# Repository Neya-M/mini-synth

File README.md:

# mini-synth

A synth but you can only play frequencies received from light, humidity, and temperature sensors.

Schematic:

two of the buttons are upside down for easier routing :P

PCB:

3D View:

BOM:

|Id|Designator|Footprint|Quantity|Designation|Supplier and ref|
|-|-|-|-|-|-|
|1|U4|QFN-20-1EP_4x4mm_P0.5mm_EP2.7x2.7mm|1|MCP23008-xML|https://www.lcsc.com/product-detail/C144211.html?spm=wm.gwc.xh.4.tp___wm.sxq.ssl.gwc&lcsc_vid=FVhWX1RURVBYAgACFQRfXlEDQ1RbBFYDRQNYU1ZfRgQxVlNeT1ZfUF1TR1BYVDsOAxUeFF5JWBYZEEoKFBINSQcJGk4NBhADEA4cHktQQlBADxALGw%3D%3D|
|2|C10|C_0402_1005Metric|1|2.2uF|https://www.lcsc.com/product-detail/C170151.html?s_z=n_q_t_capacitor%25200402&spm=wm.fly.bg.0.xh___wm.ssy.tc.0.tz&lcsc_vid=FVhWX1RURVBYAgACFQRfXlEDQ1RbBFYDRQNYU1ZfRgQxVlNeT1laVVVURlVcXjsOAxUeFF5JWBYZEEoKFBINSQcJGk4NBhYS|
|3|SW3|RotaryEncoder_Alps_EC12E-Switch_Vertical_H20mm|1|volume|https://www.lcsc.com/product-detail/C255515.html?s_z=n_q_t_ec12e&spm=wm.fly.bg.3.stp___wm.ssy.tc.0.tz&lcsc_vid=FVhWX1RURVBYAgACFQRfXlEDQ1RbBFYDRQNYU1ZfRgQxVlNeT1laVFdVQ1BcVTsOAxUeFF5JWBYZEEoKFBINSQcJGk4NBhADEA4cHktQR1BADxALGw%3D%3D|
|4|J4|PinHeader_1x04_P2.54mm_Vertical|1|weaker pins|no part|
|5|"C31|C32|C17|C3|C2|C4|C13|C18|C1|C19|C16|C6"|C_0402_1005Metric|12|100nF|https://www.lcsc.com/product-detail/C60474.html?s_z=n_q_t_capacitor%25200402&spm=wm.fly.bg.0.xh___wm.ssy.tc.0.tz&lcsc_vid=FVhWX1RURVBYAgACFQRfXlEDQ1RbBFYDRQNYU1ZfRgQxVlNeT1laVVVURlVcXjsOAxUeFF5JWBYZEEoKFBINSQcJGk4NBhYS|
|6|"R19|R5|R11|R8|R6"|R_0402_1005Metric|5|10K|https://www.lcsc.com/product-detail/C60490.html?s_z=n_q_t_resistor%25200402&spm=wm.fly.bg.0.xh___wm.ssy.tc.0.tz&lcsc_vid=FVhWX1RURVBYAgACFQRfXlEDQ1RbBFYDRQNYU1ZfRgQxVlNeT1laVFFRTlRWUDsOAxUeFF5JWBYZEEoKFBINSQcJGk4NBhADEA4cHktXRlVcSQwSGg0%3D|
|7|"C8|C9|C7"|C_0402_1005Metric|3|1uF|https://www.lcsc.com/product-detail/C87145.html?s_z=n_q_t_capacitor%25200402&spm=wm.fly.bg.0.xh___wm.ssy.tc.0.tz&lcsc_vid=FVhWX1RURVBYAgACFQRfXlEDQ1RbBFYDRQNYU1ZfRgQxVlNeT1laVVVURlVcXjsOAxUeFF5JWBYZEEoKFBINSQcJGk4NBhYS|
|8|"REF**|REF**|REF**"|capacitive touch button 10mm|3|capacitive touch button 10mm|no part|
|9|R21|SW-TH_PRS11R-415F-S103B1|1|20K|https://www.lcsc.com/product-detail/C17371045.html?spm=wm.gwc.xh.9.cbm___wm.sxq.ssl.gwc&lcsc_vid=FVhWX1RURVBYAgACFQRfXlEDQ1RbBFYDRQNYU1ZfRgQxVlNeT1ZfUF1TR1BYVDsOAxUeFF5JWBYZEEoKFBINSQcJGk4NBhADEA4cHktQQlBADxALGw%3D%3D|
|10|R1|R_LDR_5.1x4.3mm_P3.4mm_Vertical|1|R_Photo|https://www.lcsc.com/product-detail/C125630.html?spm=wm.gwc.xh.10.cbm___wm.sxq.ssl.gwc&lcsc_vid=FVhWX1RURVBYAgACFQRfXlEDQ1RbBFYDRQNYU1ZfRgQxVlNeT1ZfUF1TR1BYVDsOAxUeFF5JWBYZEEoKFBINSQcJGk4NBhADEA4cHktQQlBADxALGw%3D%3D|
|11|U7|WQFN-16-1EP_3x3mm_P0.5mm_EP1.6x1.6mm_ThermalVias|1|TPA6132A2RTE|https://www.lcsc.com/product-detail/C69901.html?s_z=n_q_TPA6132A2RTE&spm=wm.fly.bg.0.xh&lcsc_vid=FVhWX1RURVBYAgACFQRfXlEDQ1RbBFYDRQNYU1ZfRgQxVlNeT1hcUFRSTlNfUjsOAxUeFF5JWBYZEEoKFBINSQcJGk4eFQsCAgIaSgADAwAHC0slQlRfV1xfR1RADxALGw%3D%3D|
|12|SW2|RotaryEncoder_Alps_EC12E-Switch_Vertical_H20mm|1|pitch|https://www.lcsc.com/product-detail/C255515.html?s_z=n_q_t_ec12e&spm=wm.fly.bg.3.stp___wm.ssy.tc.0.tz&lcsc_vid=FVhWX1RURVBYAgACFQRfXlEDQ1RbBFYDRQNYU1ZfRgQxVlNeT1laVFdVQ1BcVTsOAxUeFF5JWBYZEEoKFBINSQcJGk4NBhADEA4cHktQR1BADxALGw%3D%3D|
|13|SW14|SW-TH_RKJXL100401V|1|SW_Rotary_1x8_MP|https://www.lcsc.com/product-detail/C160838.html?spm=wm.gwc.xh.3.tp___wm.sxq.ssl.gwc&lcsc_vid=FVhWX1RURVBYAgACFQRfXlEDQ1RbBFYDRQNYU1ZfRgQxVlNeT1ZfUF1TR1BYVDsOAxUeFF5JWBYZEEoKFBINSQcJGk4NBhADEA4cHktQQlBADxALGw%3D%3D|
|14|"C11|C12|C5"|C_0402_1005Metric|3|4.7uF|https://www.lcsc.com/product-detail/C368809.html?s_z=n_q_t_capacitor%25200402&spm=wm.fly.bg.2.xh___wm.ssy.tc.0.tz&lcsc_vid=FVhWX1RURVBYAgACFQRfXlEDQ1RbBFYDRQNYU1ZfRgQxVlNeT1laVVVURlVcXjsOAxUeFF5JWBYZEEoKFBINSQcJGk4NBhYS|
|15|C25|C_0402_1005Metric|1|4.7uF|https://www.lcsc.com/product-detail/C368809.html?s_z=n_q_t_capacitor%25200402&spm=wm.fly.bg.2.xh___wm.ssy.tc.0.tz&lcsc_vid=FVhWX1RURVBYAgACFQRfXlEDQ1RbBFYDRQNYU1ZfRgQxVlNeT1laVVVURlVcXjsOAxUeFF5JWBYZEEoKFBINSQcJGk4NBhYS|
|16|SW7|SW-SMD_L6.1-W3.7-LS8.0-1|1|BOOT|https://www.lcsc.com/product-detail/C49234126.html?spm=wm.gwc.xh.0.tp___wm.sxq.ssl.gwc&lcsc_vid=FVhWX1RURVBYAgACFQRfXlEDQ1RbBFYDRQNYU1ZfRgQxVlNeT1ZfUF1TR1BYVDsOAxUeFF5JWBYZEEoKFBINSQcJGk4NBhADEA4cHktQQlBADxALGw%3D%3D|
|17|"R13|R12|R9|R7"|R_0402_1005Metric|4|15K|https://www.lcsc.com/product-detail/C2909322.html?s_z=n_q_t_resistor%25200402&spm=wm.fly.bg.0.stp___wm.ssy.tc.0.tz&lcsc_vid=FVhWX1RURVBYAgACFQRfXlEDQ1RbBFYDRQNYU1ZfRgQxVlNeT1laVFFRTlRWUDsOAxUeFF5JWBYZEEoKFBINSQcJGk4NBhADEA4cHktXRlVcSQwSGg0%3D|
|18|"D8|D3|D1|D5|D4|D7|D6|D2"|LED-SMD_4P-L3.2-W2.8-LS5.9_SK6812MINI-E|8|SK6812|https://www.lcsc.com/product-detail/C5149201.html?s_z=n_q_l_SK6812%2520mini%2520e&spm=wm.fly.bg.9.stp___wm.ssy.ml.0-0.ent&lcsc_vid=FVhWX1RURVBYAgACFQRfXlEDQ1RbBFYDRQNYU1ZfRgQxVlNeT1hcUV1XQ1ZdUzsOAxUeFF5JWBYZEEoKFBINSQcJGk4NBhADEA4cHktSR1dADxALGw%3D%3D|
|19|U6|TSSOP-14_L5.0-W4.4-P0.65-LS6.4-BL|1|"74HCT125PW|118"|https://www.lcsc.com/product-detail/C131316.html?spm=wm.gwc.xh.10.cbm___wm.sxq.ssl.gwc&lcsc_vid=FVhWX1RURVBYAgACFQRfXlEDQ1RbBFYDRQNYU1ZfRgQxVlNeT1hcUVNRQVZYUTsOAxUeFF5JWBYZEEoKFBINSQcJGk4NBhYS|
|20|J1|USB-C-SMD_G-SWITCH_GT-USB-7010ASV|1|USB_C_Receptacle_USB2.0_14P|https://www.lcsc.com/product-detail/C2988369.html?spm=wm.gwc.xh.2.cbm___wm.sxq.ssl.gwc&lcsc_vid=FVhWX1RURVBYAgACFQRfXlEDQ1RbBFYDRQNYU1ZfRgQxVlNeT1ZfUF1TR1BYVDsOAxUeFF5JWBYZEEoKFBINSQcJGk4NBhADEA4cHktQQlBADxALGw%3D%3D|
|21|SW1|KEY-TH_L12.0-W3.3-P5.00|1|reset|https://www.lcsc.com/product-detail/C2888728.html?spm=wm.gwc.xh.8.tp___wm.sxq.ssl.gwc&lcsc_vid=FVhWX1RURVBYAgACFQRfXlEDQ1RbBFYDRQNYU1ZfRgQxVlNeT1ZfUF1TR1BYVDsOAxUeFF5JWBYZEEoKFBINSQcJGk4NBhADEA4cHktQQlBADxALGw%3D%3D|
|22|R20|R_0402_1005Metric|1|330|https://www.lcsc.com/product-detail/C105875.html?s_z=n_q_t_resistor%25200402&spm=wm.fly.bg.0.xh___wm.ssy.tc.0.tz&lcsc_vid=FVhWX1RURVBYAgACFQRfXlEDQ1RbBFYDRQNYU1ZfRgQxVlNeT1laVFFRTlRWUDsOAxUeFF5JWBYZEEoKFBINSQcJGk4NBhADEA4cHktXRlVcSQwSGg0%3D|
|23|"D10|D16|D9|D11|D14|D12|D13|D17|D15"|D_0402_1005Metric|9|D|https://www.lcsc.com/product-detail/C28646371.html?s_z=n_q_t_diode&spm=wm.fly.bg.0.stp___wm.ssy.tc.1.tz&lcsc_vid=FVhWX1RURVBYAgACFQRfXlEDQ1RbBFYDRQNYU1ZfRgQxVlNeT1hcX1NVT1ldXjsOAxUeFF5JWBYZEEoKFBINSQcJGk4eFQsCAgIaSgADAwAHC0slRlVeUFxUWQkaCgg%3D|
|24|R22|R_0402_1005Metric|1|1K|https://www.lcsc.com/product-detail/C106235.html?s_z=n_q_t_resistor%25200402&spm=wm.fly.bg.0.xh___wm.ssy.tc.0.tz&lcsc_vid=FVhWX1RURVBYAgACFQRfXlEDQ1RbBFYDRQNYU1ZfRgQxVlNeT1laVFFRTlRWUDsOAxUeFF5JWBYZEEoKFBINSQcJGk4NBhADEA4cHktXRlVcSQwSGg0%3D|
|25|SW9|SW-TH_XKB5858-Z-E|1|loop 2|https://www.lcsc.com/product-detail/C780038.html?spm=wm.gwc.xh.7.cbm___wm.sxq.ssl.gwc&lcsc_vid=FVhWX1RURVBYAgACFQRfXlEDQ1RbBFYDRQNYU1ZfRgQxVlNeT1ZfUF1TR1BYVDsOAxUeFF5JWBYZEEoKFBINSQcJGk4NBhADEA4cHktQQlBADxALGw%3D%3D|
|26|CN1|AUDIO-TH_HOOYA_PJ-320|1|trs headphone jack|https://www.lcsc.com/product-detail/C2939180.html?s_z=n_q_C2939180&globalKeyword=C2939180|
|27|U5|LQFP-48_7x7mm_P0.5mm|1|CH32V203C8T6|https://www.lcsc.com/product-detail/C3001172.html?spm=wm.gwc.xh.11.cbm___wm.sxq.ssl.gwc&lcsc_vid=FVhWX1RURVBYAgACFQRfXlEDQ1RbBFYDRQNYU1ZfRgQxVlNeT1hcUVNRQVZYUTsOAxUeFF5JWBYZEEoKFBINSQcJGk4NBhYS|
|28|"C30|C29"|C_0402_1005Metric|2|10uF|https://www.lcsc.com/product-detail/C315248.html?s_z=n_q_t_capacitor%25200402&spm=wm.fly.bg.0.xh___wm.ssy.tc.0.tz&lcsc_vid=FVhWX1RURVBYAgACFQRfXlEDQ1RbBFYDRQNYU1ZfRgQxVlNeT1laVVVURlVcXjsOAxUeFF5JWBYZEEoKFBINSQcJGk4NBhYS|
|29|C23|C_0402_1005Metric|1|10uF|https://www.lcsc.com/product-detail/C315248.html?s_z=n_q_t_capacitor%25200402&spm=wm.fly.bg.0.xh___wm.ssy.tc.0.tz&lcsc_vid=FVhWX1RURVBYAgACFQRfXlEDQ1RbBFYDRQNYU1ZfRgQxVlNeT1laVVVURlVcXjsOAxUeFF5JWBYZEEoKFBINSQcJGk4NBhYS|
|30|U2|Sensirion_DFN-4_1.5x1.5mm_P0.8mm_SHT4x_NoCentralPad|1|SHT4x|https://www.lcsc.com/product-detail/C55108905.html?s_z=n_q_t_sht4&spm=wm.fly.bg.0.xh___wm.ssy.tc.0.tz&lcsc_vid=FVhWX1RURVBYAgACFQRfXlEDQ1RbBFYDRQNYU1ZfRgQxVlNeT1hcUVdfRVdZUDsOAxUeFF5JWBYZEEoKFBINSQcJGk4NBhADEA4cHktQR1RADxALGw%3D%3D|
|31|"C24|C21"|C_0402_1005Metric|2|560pF|https://www.lcsc.com/product-detail/C315248.html?s_z=n_q_t_capacitor%25200402&spm=wm.fly.bg.0.xh___wm.ssy.tc.0.tz&lcsc_vid=FVhWX1RURVBYAgACFQRfXlEDQ1RbBFYDRQNYU1ZfRgQxVlNeT1laVVVURlVcXjsOAxUeFF5JWBYZEEoKFBINSQcJGk4NBhYS|
|32|"C14|C15"|C_0402_1005Metric|2|47uf|https://www.lcsc.com/product-detail/C140782.html?s_z=n_q_t_47%2520uF%2520capacitor&spm=wm.fly.bg.5.xh___wm.ssy.tc.0.tz&lcsc_vid=FVhWX1RURVBYAgACFQRfXlEDQ1RbBFYDRQNYU1ZfRgQxVlNeT1hcUFJXQ1VfUDsOAxUeFF5JWBYZEEoKFBINSQcJGk4NBhADEA4cHktXRlVeSQwSGg0%3D|
|33|"R16|R15"|R_0402_1005Metric|2|27|https://www.lcsc.com/product-detail/C2100055.html?s_z=n_q_t_resistor%25200402&spm=wm.fly.bg.0.xh___wm.ssy.tc.0.tz&lcsc_vid=FVhWX1RURVBYAgACFQRfXlEDQ1RbBFYDRQNYU1ZfRgQxVlNeT1laVFFRTlRWUDsOAxUeFF5JWBYZEEoKFBINSQcJGk4NBhADEA4cHktXRlVcSQwSGg0%3D|
|34|U3|SOT-23|1|MCP1700x-330xxTT|https://www.lcsc.com/product-detail/C144211.html?spm=wm.gwc.xh.4.cbm___wm.fly.ssl.gwc&lcsc_vid=FVhWX1RURVBYAgACFQRfXlEDQ1RbBFYDRQNYU1ZfRgQxVlNeT1hcUVdWTlZWVTsOAxUeFF5JWBYZEEoKFBINSQcJGk4eFQsCAgIaSgADAwAHC0slT1VXUVdIHxUDCw%3D%3D|
|35|SW10|SW-TH_XKB5858-Z-E|1|record|https://www.lcsc.com/product-detail/C780038.html?spm=wm.gwc.xh.7.cbm___wm.sxq.ssl.gwc&lcsc_vid=FVhWX1RURVBYAgACFQRfXlEDQ1RbBFYDRQNYU1ZfRgQxVlNeT1ZfUF1TR1BYVDsOAxUeFF5JWBYZEEoKFBINSQcJGk4NBhADEA4cHktQQlBADxALGw%3D%3D|
|36|"R4|R18|R17"|R_0402_1005Metric|3|4.7K|https://www.lcsc.com/product-detail/C105871.html?s_z=n_q_t_resistor%25200402&spm=wm.fly.bg.0.xh___wm.ssy.tc.0.tz&lcsc_vid=FVhWX1RURVBYAgACFQRfXlEDQ1RbBFYDRQNYU1ZfRgQxVlNeT1laVFFRTlRWUDsOAxUeFF5JWBYZEEoKFBINSQcJGk4NBhADEA4cHktXRlVcSQwSGg0%3D|
|37|SW12|KEY-TH_L12.0-W3.3-P5.00|1|free1|https://www.lcsc.com/product-detail/C2888728.html?spm=wm.gwc.xh.8.tp___wm.sxq.ssl.gwc&lcsc_vid=FVhWX1RURVBYAgACFQRfXlEDQ1RbBFYDRQNYU1ZfRgQxVlNeT1ZfUF1TR1BYVDsOAxUeFF5JWBYZEEoKFBINSQcJGk4NBhADEA4cHktQQlBADxALGw%3D%3D|
|38|SW11|KEY-TH_L12.0-W3.3-P5.00|1|delay|https://www.lcsc.com/product-detail/C2888728.html?spm=wm.gwc.xh.8.tp___wm.sxq.ssl.gwc&lcsc_vid=FVhWX1RURVBYAgACFQRfXlEDQ1RbBFYDRQNYU1ZfRgQxVlNeT1ZfUF1TR1BYVDsOAxUeFF5JWBYZEEoKFBINSQcJGk4NBhADEA4cHktQQlBADxALGw%3D%3D|
|39|"R3|R2"|R_0402_1005Metric|2|5.1K|https://www.lcsc.com/product-detail/C105872.html?s_z=n_q_t_resistor%25200402&spm=wm.fly.bg.0.xh___wm.ssy.tc.0.tz&lcsc_vid=FVhWX1RURVBYAgACFQRfXlEDQ1RbBFYDRQNYU1ZfRgQxVlNeT1laVFFRTlRWUDsOAxUeFF5JWBYZEEoKFBINSQcJGk4NBhADEA4cHktXRlVcSQwSGg0%3D|
|40|SW13|KEY-TH_L12.0-W3.3-P5.00|1|free2|https://www.lcsc.com/product-detail/C2888728.html?spm=wm.gwc.xh.8.tp___wm.sxq.ssl.gwc&lcsc_vid=FVhWX1RURVBYAgACFQRfXlEDQ1RbBFYDRQNYU1ZfRgQxVlNeT1ZfUF1TR1BYVDsOAxUeFF5JWBYZEEoKFBINSQcJGk4NBhADEA4cHktQQlBADxALGw%3D%3D|
|41|R14|R_0402_1005Metric|1|100K|https://www.lcsc.com/product-detail/C60491.html?s_z=n_q_t_resistor%25200402&spm=wm.fly.bg.0.xh___wm.ssy.tc.0.tz&lcsc_vid=FVhWX1RURVBYAgACFQRfXlEDQ1RbBFYDRQNYU1ZfRgQxVlNeT1laVFFRTlRWUDsOAxUeFF5JWBYZEEoKFBINSQcJGk4NBhADEA4cHktXRlVcSQwSGg0%3D|
|42|"FB2|FB1"|L0402|2|FerriteBead_Small|https://www.lcsc.com/product-detail/C17701320.html?spm=wm.gwc.xh.5.tp___wm.sxq.ssl.gwc&lcsc_vid=FVhWX1RURVBYAgACFQRfXlEDQ1RbBFYDRQNYU1ZfRgQxVlNeT1ZfUF1TR1BYVDsOAxUeFF5JWBYZEEoKFBINSQcJGk4NBhADEA4cHktQQlBADxALGw%3D%3D|
|43|C22|C_0402_1005Metric|1|10nF|https://www.lcsc.com/product-detail/C15195.html?s_z=n_q_t_capacitor%25200402&spm=wm.fly.bg.0.stp___wm.ssy.tc.0.tz&lcsc_vid=FVhWX1RURVBYAgACFQRfXlEDQ1RbBFYDRQNYU1ZfRgQxVlNeT1laVVVURlVcXjsOAxUeFF5JWBYZEEoKFBINSQcJGk4NBhYS|
|44|U1|DIP-16_W7.62mm|1|PT2399|https://www.lcsc.com/product-detail/C84963.html?s_z=n_q_x_pt2399&spm=wm.ssy.em.0.tz&lcsc_vid=FVhWX1RURVBYAgACFQRfXlEDQ1RbBFYDRQNYU1ZfRgQxVlNeT1hcUVZSQFlfVDsOAxUeFF5JWBYZEEoKFBINSQcJGk4eFQsCAgIaSgADAwAHC0slRVheUFRWT08GEwkK|
|45|"C20|C26"|C_0402_1005Metric|2|5.6nF|https://www.lcsc.com/product-detail/C281760.html?s_z=n_q_t_capacitor%25200402&spm=wm.fly.bg.0.xh___wm.ssy.tc.0.tz&lcsc_vid=FVhWX1RURVBYAgACFQRfXlEDQ1RbBFYDRQNYU1ZfRgQxVlNeT1laVVVURlVcXjsOAxUeFF5JWBYZEEoKFBINSQcJGk4NBhYS|
|46|J2|PinHeader_1x02_P2.54mm_Vertical|1|analog|no part|
|47|SW8|SW-SMD_L6.1-W3.7-LS8.0-1|1|RESET|https://www.lcsc.com/product-detail/C49234126.html?spm=wm.gwc.xh.0.tp___wm.sxq.ssl.gwc&lcsc_vid=FVhWX1RURVBYAgACFQRfXlEDQ1RbBFYDRQNYU1ZfRgQxVlNeT1ZfUF1TR1BYVDsOAxUeFF5JWBYZEEoKFBINSQcJGk4NBhADEA4cHktQQlBADxALGw%3D%3D|
|48|"C28|C27"|C_0402_1005Metric|2|12pF|https://www.lcsc.com/product-detail/C26406.html?s_z=n_q_t_capacitor%25200402&spm=wm.fly.bg.0.xh___wm.ssy.tc.0.tz&lcsc_vid=FVhWX1RURVBYAgACFQRfXlEDQ1RbBFYDRQNYU1ZfRgQxVlNeT1laVVVURlVcXjsOAxUeFF5JWBYZEEoKFBINSQcJGk4NBhYS|
|49|Y1|CRYSTAL-SMD_4P-L3.2-W2.5-BL|1|8MHz|https://www.lcsc.com/product-detail/C2682775.html?spm=wm.gwc.xh.1.cbm___wm.sxq.ssl.gwc&lcsc_vid=FVhWX1RURVBYAgACFQRfXlEDQ1RbBFYDRQNYU1ZfRgQxVlNeT1ZfUF1TR1BYVDsOAxUeFF5JWBYZEEoKFBINSQcJGk4NBhADEA4cHktQQlBADxALGw%3D%3D|
|50|SW4|SW-SMD_L6.1-W3.7-LS8.0-1|1|reset2|https://www.lcsc.com/product-detail/C49234126.html?spm=wm.gwc.xh.0.tp___wm.sxq.ssl.gwc&lcsc_vid=FVhWX1RURVBYAgACFQRfXlEDQ1RbBFYDRQNYU1ZfRgQxVlNeT1ZfUF1TR1BYVDsOAxUeFF5JWBYZEEoKFBINSQcJGk4NBhADEA4cHktQQlBADxALGw%3D%3D|
|51|R10|R_0603_1608Metric|1|2.7K|https://www.lcsc.com/product-detail/C2907008.html?s_z=n_q_t_resistor%25200603%25202.7k&spm=wm.fly.bg.0.xh___wm.ssy.tc.0.tz&lcsc_vid=FVhWX1RURVBYAgACFQRfXlEDQ1RbBFYDRQNYU1ZfRgQxVlNeT1hcUVZWT1haVjsOAxUeFF5JWBYZEEoKFBINSQcJGk4NBhADEA4cHktXRlhXSQwSGg0%3D|
|52|J3|PinHeader_1x04_P2.54mm_Vertical|1|debug header|no part|

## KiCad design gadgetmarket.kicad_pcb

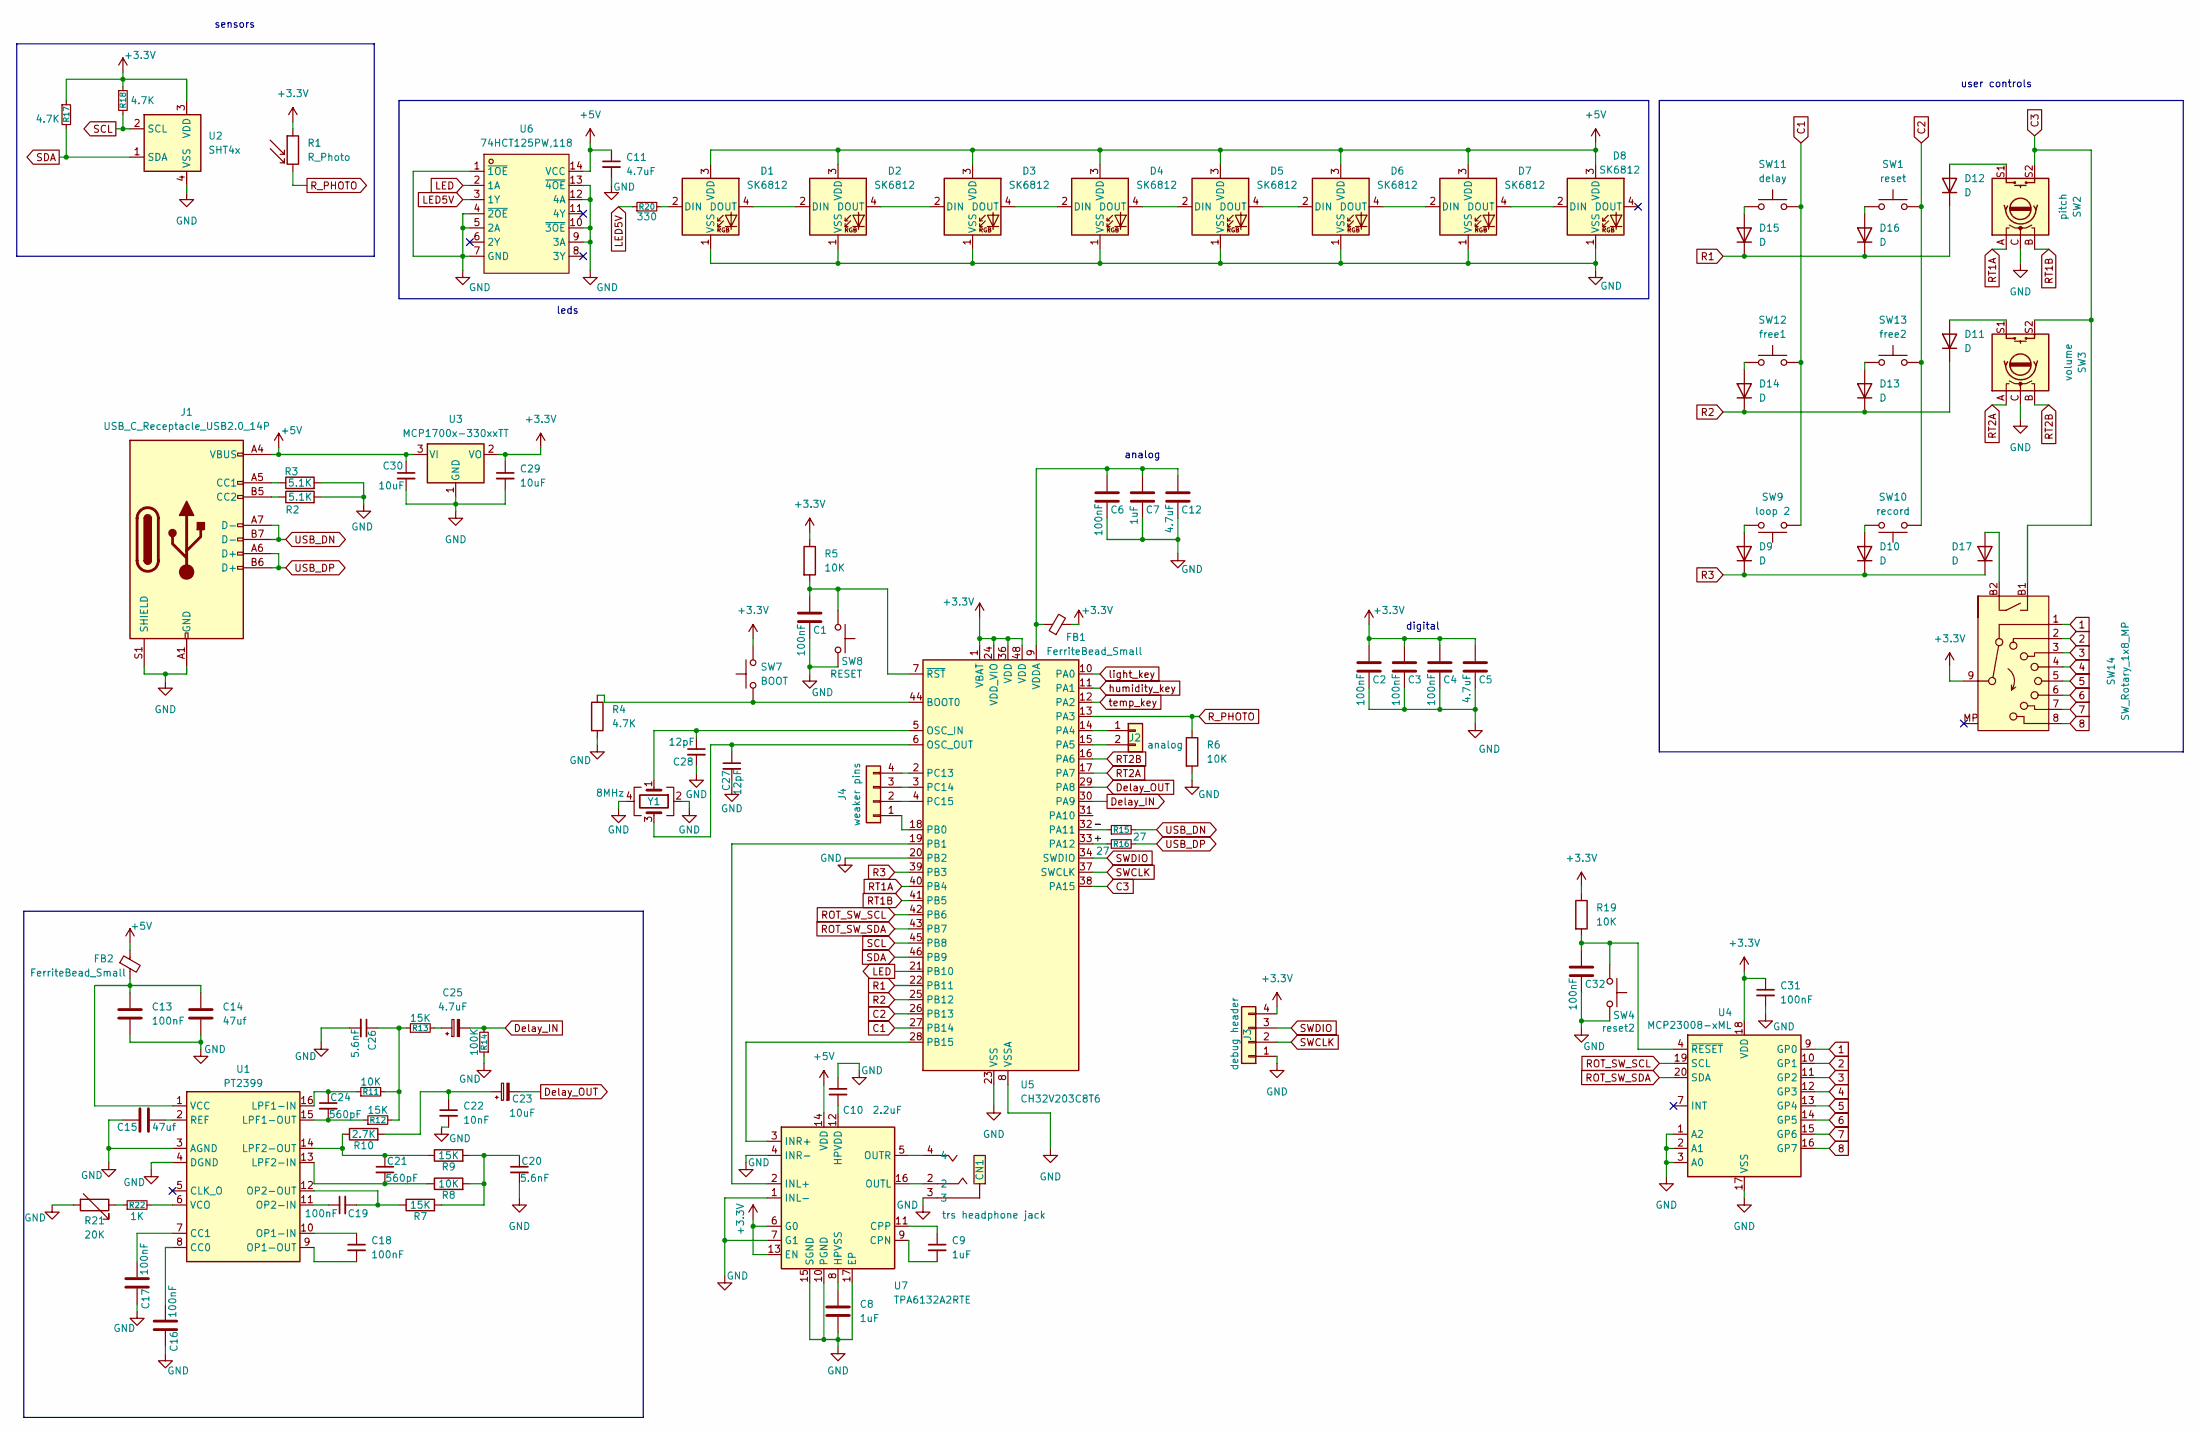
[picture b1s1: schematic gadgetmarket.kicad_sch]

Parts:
C1, C2, C3, C4, C6, C13, C16, C17, C18, C19, C31, C32: 100nF; C_0402_1005Metric
C5, C11, C12, C25: 4.7uF; C_0402_1005Metric
C7, C8, C9: 1uF; C_0402_1005Metric
C10: 2.2uF; C_0402_1005Metric
C14, C15: 47uf; C_0603_1608Metric
C20, C26: 5.6nF; C_0402_1005Metric
C21, C24: 560pF; C_0402_1005Metric
C22: 10nF; C_0402_1005Metric
C23, C29, C30: 10uF; C_0402_1005Metric
C27, C28: 12pF; C_0402_1005Metric
CN1: trs headphone jack; AUDIO-TH_HOOYA_PJ-320; MPN PJ-320(OS); LCSC Part C2939180
D1, D2, D3, D4, D5, D6, D7, D8: SK6812; LED-SMD_4P-L3.2-W2.8-LS5.9_SK6812MINI-E
D9, D10, D11, D12, D13, D14, D15, D16, D17: D; D_0402_1005Metric
FB1, FB2: FerriteBead_Small; L0402
J1: USB_C_Receptacle_USB2.0_14P; USB-C-SMD_G-SWITCH_GT-USB-7010ASV
J2: analog; PinHeader_1x02_P2.54mm_Vertical
J3: debug header; PinHeader_1x04_P2.54mm_Vertical
J4: weaker pins; PinHeader_1x04_P2.54mm_Vertical
R1: R_Photo; R_LDR_5.1x4.3mm_P3.4mm_Vertical
R2, R3: 5.1K; R_0402_1005Metric
R4, R17, R18: 4.7K; R_0402_1005Metric
R5, R6, R8, R11, R19: 10K; R_0402_1005Metric
R7, R9, R12, R13: 15K; R_0402_1005Metric
R10: 2.7K; R_0603_1608Metric
R14: 100K; R_0402_1005Metric
R15, R16: 27; R_0402_1005Metric
R20: 330; R_0402_1005Metric
R21: 20K; SW-TH_PRS11R-415F-S103B1
R22: 1K; R_0402_1005Metric
SW1: reset; KEY-TH_L12.0-W3.3-P5.00
SW2: pitch; RotaryEncoder_Alps_EC12E-Switch_Vertical_H20mm
SW3: volume; RotaryEncoder_Alps_EC12E-Switch_Vertical_H20mm
SW4: reset2; SW-SMD_L6.1-W3.7-LS8.0-1
SW7: BOOT; SW-SMD_L6.1-W3.7-LS8.0-1
SW8: RESET; SW-SMD_L6.1-W3.7-LS8.0-1
SW9: loop 2; SW-TH_XKB5858-Z-E
SW10: record; SW-TH_XKB5858-Z-E
SW11: delay; KEY-TH_L12.0-W3.3-P5.00
SW12: free1; KEY-TH_L12.0-W3.3-P5.00
SW13: free2; KEY-TH_L12.0-W3.3-P5.00
SW14: SW_Rotary_1x8_MP; SW-TH_RKJXL100401V
U1: PT2399; DIP-16_W7.62mm
U2: SHT4x; Sensirion_DFN-4_1.5x1.5mm_P0.8mm_SHT4x_NoCentralPad
U3: MCP1700x-330xxTT; SOT-23
U4: MCP23008-xML; QFN-20-1EP_4x4mm_P0.5mm_EP2.7x2.7mm
U5: CH32V203C8T6; LQFP-48_7x7mm_P0.5mm
U6: 74HCT125PW,118; TSSOP-14_L5.0-W4.4-P0.65-LS6.4-BL; MPN 74HCT125PW,118; LCSC Part C131316
U7: TPA6132A2RTE; WQFN-16-1EP_3x3mm_P0.5mm_EP1.6x1.6mm_ThermalVias
Y1: 8MHz; CRYSTAL-SMD_4P-L3.2-W2.5-BL

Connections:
1: SW14.1, U4.9 (GP0)
2: SW14.2, U4.10 (GP1)
3: SW14.3, U4.11 (GP2)
4: SW14.4, U4.12 (GP3)
5: SW14.5, U4.13 (GP4)
6: SW14.6, U4.14 (GP5)
7: SW14.7, U4.15 (GP6)
8: SW14.8, U4.16 (GP7)
+3.3V: C2.1, C3.1, C4.1, C5.1, C29.1, C31.1, FB1.2, J3.4, R1.1, R5.1, R17.1, R18.1, R19.1, SW7.2, SW14.9, U2.3 (VDD), U3.2 (VO), U4.18 (VDD), U5.1 (VBAT), U5.24 (VDD_VIO), U5.36 (VDD), U5.48 (VDD), U7.6 (G0), U7.13 (EN)
+5V: C11.1, C30.1, D1.3 (VDD), D2.3 (VDD), D3.3 (VDD), D4.3 (VDD), D5.3 (VDD), D6.3 (VDD), D7.3 (VDD), D8.3 (VDD), FB2.1, J1.A4 (VBUS), J1.A9 (VBUS), J1.B4 (VBUS), J1.B9 (VBUS), U3.3 (VI), U6.14 (VCC), U7.14 (VDD)
/+: R16.1, U5.33 (PA12)
/-: R15.1, U5.32 (PA11)
C1: SW9.4, SW11.2, SW12.2, U5.27 (PB14)
C2: SW1.2, SW10.4, SW13.2, U5.26 (PB13)
C3: SW2.S2, SW3.S2, SW14.B1, U5.38 (PA15)
Delay_IN: C25.2, R14.2, U5.30 (PA9)
Delay_OUT: C23.2, U5.29 (PA8)
GND: C1.2, C2.2, C3.2, C4.2, C5.2, C6.2, C7.2, C8.2, C10.1, C11.2, C12.2, C13.2, C14.2, C15.1, C16.2, C17.2, C20.2, C22.2, C26.2, C27.2, C28.2, C29.2, C30.2, C31.2, C32.2, CN1.3, D1.1 (VSS), D2.1 (VSS), D3.1 (VSS), D4.1 (VSS), D5.1 (VSS), D6.1 (VSS), D7.1 (VSS), D8.1 (VSS), J1.A1 (GND), J1.A12 (GND), J1.B1 (GND), J1.B12 (GND), J1.S1 (SHIELD), J3.1, R2.2, R3.2, R4.2, R6.2, R14.1, R21.2, SW2.C, SW3.C, SW4.2, SW8.2, U1.3 (AGND), U1.4 (DGND), U2.4 (VSS), U3.1 (GND), U4.1 (A2), U4.2 (A1), U4.3 (A0), U4.17 (VSS), U4.21, U5.8 (VSSA), U5.20 (PB2), U5.23 (VSS), U5.35 (VSS), U5.47 (VSS), U6.1 (~1OE), U6.4 (~2OE), U6.5 (2A), U6.7 (GND), U6.9 (3A), U6.10 (~3OE), U6.12 (4A), U6.13 (~4OE), U7.1 (INL-), U7.4 (INR-), U7.7 (G1), U7.10 (PGND), U7.15 (SGND), U7.17 (EP), Y1.2, Y1.4
LED: U5.21 (PB10), U6.2 (1A)
LED5V: R20.1, U6.3 (1Y)
unnamed: C20.1, R7.2, R8.2, R9.2
unnamed: C22.1, C23.1, R10.2
unnamed: C25.1, R13.2
unnamed: C26.1, R11.2, R12.2, R13.1
unnamed: D1.2 (DIN), R20.2
unnamed: D1.4 (DOUT), D2.2 (DIN)
unnamed: D2.4 (DOUT), D3.2 (DIN)
unnamed: D3.4 (DOUT), D4.2 (DIN)
unnamed: D4.4 (DOUT), D5.2 (DIN)
unnamed: D5.4 (DOUT), D6.2 (DIN)
unnamed: D6.4 (DOUT), D7.2 (DIN)
unnamed: D7.4 (DOUT), D8.2 (DIN)
unnamed: D9.2 (A), SW9.2
unnamed: D10.2 (A), SW10.2
unnamed: D11.2 (A), SW3.S1
unnamed: D12.2 (A), SW2.S1
unnamed: D13.2 (A), SW13.1
unnamed: D14.2 (A), SW12.1
unnamed: D15.2 (A), SW11.1
unnamed: D16.2 (A), SW1.1
unnamed: D17.2 (A), SW14.B2
unnamed: J1.A5 (CC1), R3.1
unnamed: J1.B5 (CC2), R2.1
unnamed: J2.1, U5.14 (PA4)
unnamed: J2.2, U5.15 (PA5)
unnamed: J4.1, U5.18 (PB0)
unnamed: J4.2, U5.4 (PC15)
unnamed: J4.3, U5.3 (PC14)
unnamed: J4.4, U5.2 (PC13)
unnamed: R21.1, R22.1
unnamed: C16.1, U1.8 (CC0)
unnamed: C17.1, U1.7 (CC1)
unnamed: C24.1, R11.1, U1.16 (LPF1-IN)
unnamed: C24.2, R12.1, U1.15 (LPF1-OUT)
unnamed: C21.2, R8.1, U1.13 (LPF2-IN)
unnamed: C21.1, R9.1, R10.1, U1.14 (LPF2-OUT)
unnamed: C18.1, U1.10 (OP1-IN)
unnamed: C18.2, U1.9 (OP1-OUT)
unnamed: C19.1, U1.11 (OP2-IN)
unnamed: C19.2, R7.1, U1.12 (OP2-OUT)
unnamed: C15.2, U1.2 (REF)
unnamed: C13.1, C14.1, FB2.2, U1.1 (VCC)
unnamed: R22.2, U1.6 (VCO)
unnamed: C32.1, R19.2, SW4.1, U4.4 (~RESET)
unnamed: R4.1, SW7.1, U5.44 (BOOT0)
unnamed: C28.1, U5.5 (OSC_IN), Y1.1
unnamed: C27.1, U5.6 (OSC_OUT), Y1.3
unnamed: U5.19 (PB1), U7.2 (INL+)
unnamed: U5.28 (PB15), U7.3 (INR+)
unnamed: C6.1, C7.1, C12.1, FB1.1, U5.9 (VDDA)
unnamed: C1.1, R5.2, SW8.1, U5.7 (~RST)
unnamed: C9.2, U7.9 (CPN)
unnamed: C9.1, U7.11 (CPP)
unnamed: C10.2, U7.12 (HPVDD)
unnamed: C8.1, U7.8 (HPVSS)
unnamed: CN1.2, U7.16 (OUTL)
unnamed: CN1.4, U7.5 (OUTR)
R1: D12.1 (K), D15.1 (K), D16.1 (K), U5.22 (PB11)
R2: D11.1 (K), D13.1 (K), D14.1 (K), U5.25 (PB12)
R3: D9.1 (K), D10.1 (K), D17.1 (K), U5.39 (PB3)
ROT_SW_SCL: U4.19 (SCL), U5.42 (PB6)
ROT_SW_SDA: U4.20 (SDA), U5.43 (PB7)
RT1A: SW2.A, U5.40 (PB4)
RT1B: SW2.B, U5.41 (PB5)
RT2A: SW3.A, U5.17 (PA7)
RT2B: SW3.B, U5.16 (PA6)
R_PHOTO: R1.2, R6.1, U5.13 (PA3)
SCL: R18.2, U2.2 (SCL), U5.45 (PB8)
SDA: R17.2, U2.1 (SDA), U5.46 (PB9)
SWCLK: J3.2, U5.37 (SWCLK)
SWDIO: J3.3, U5.34 (SWDIO)
USB_DN: J1.A7 (D-), J1.B7 (D-), R15.2
USB_DP: J1.A6 (D+), J1.B6 (D+), R16.2
humidity_key: U5.11 (PA1)
light_key: U5.10 (PA0)
temp_key: U5.12 (PA2)

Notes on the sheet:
digital
sensors
user controls
leds
analog

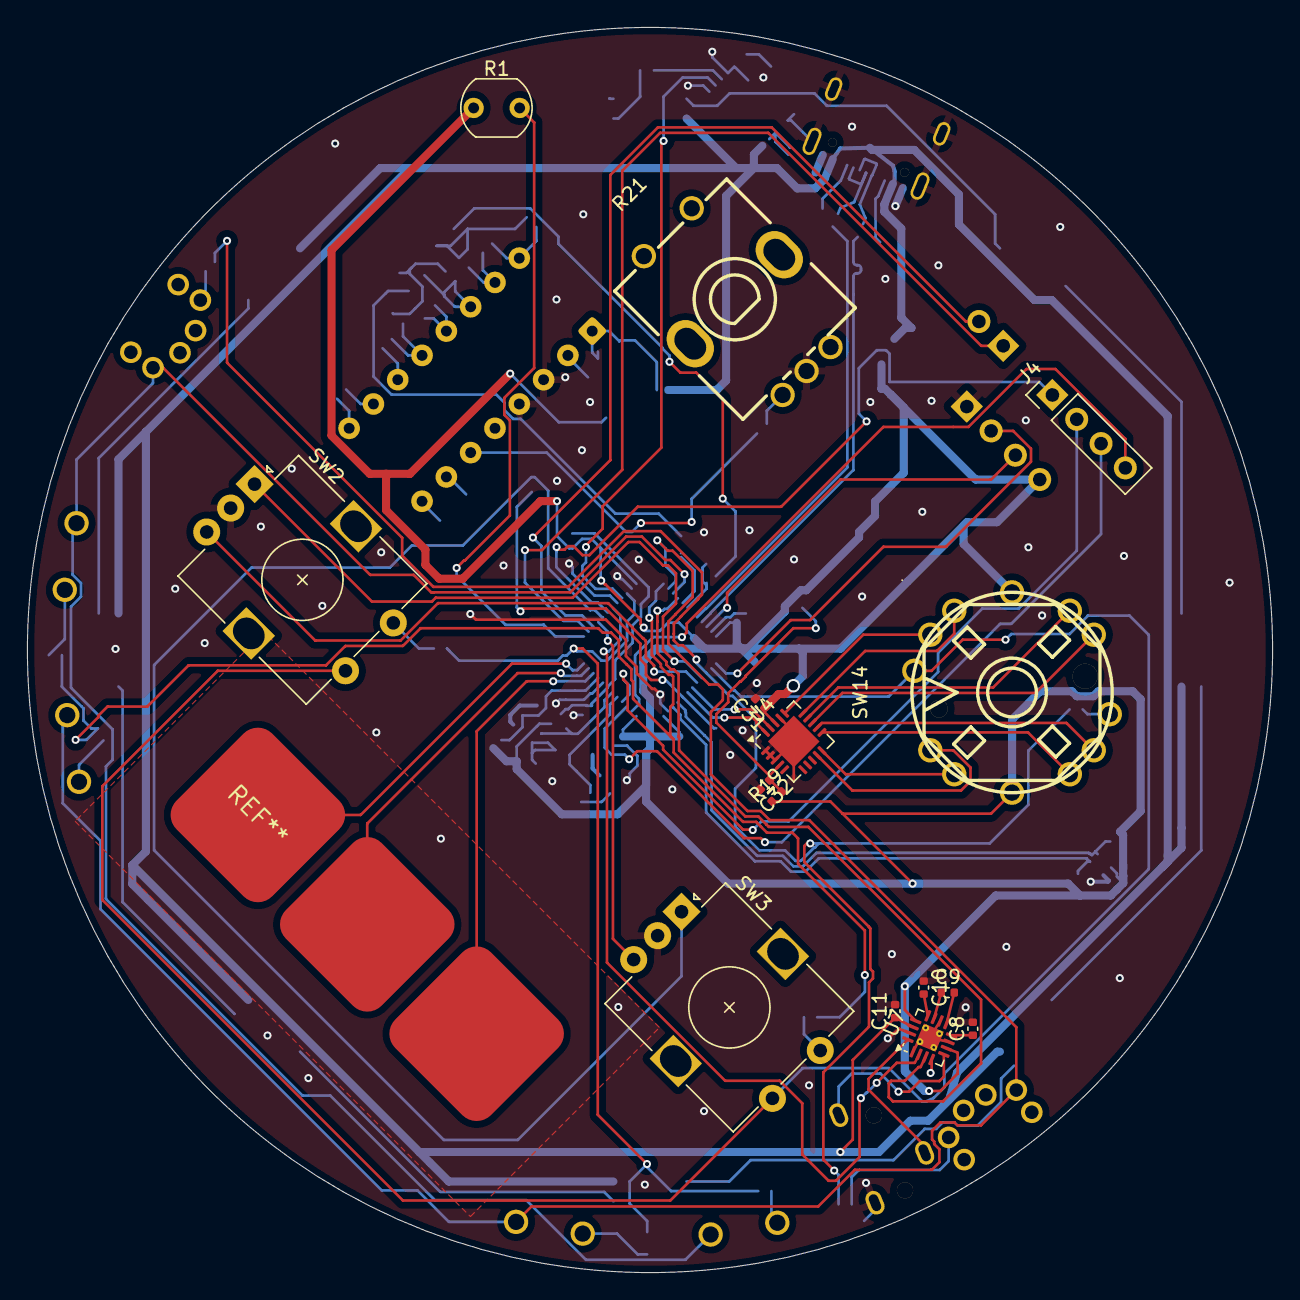
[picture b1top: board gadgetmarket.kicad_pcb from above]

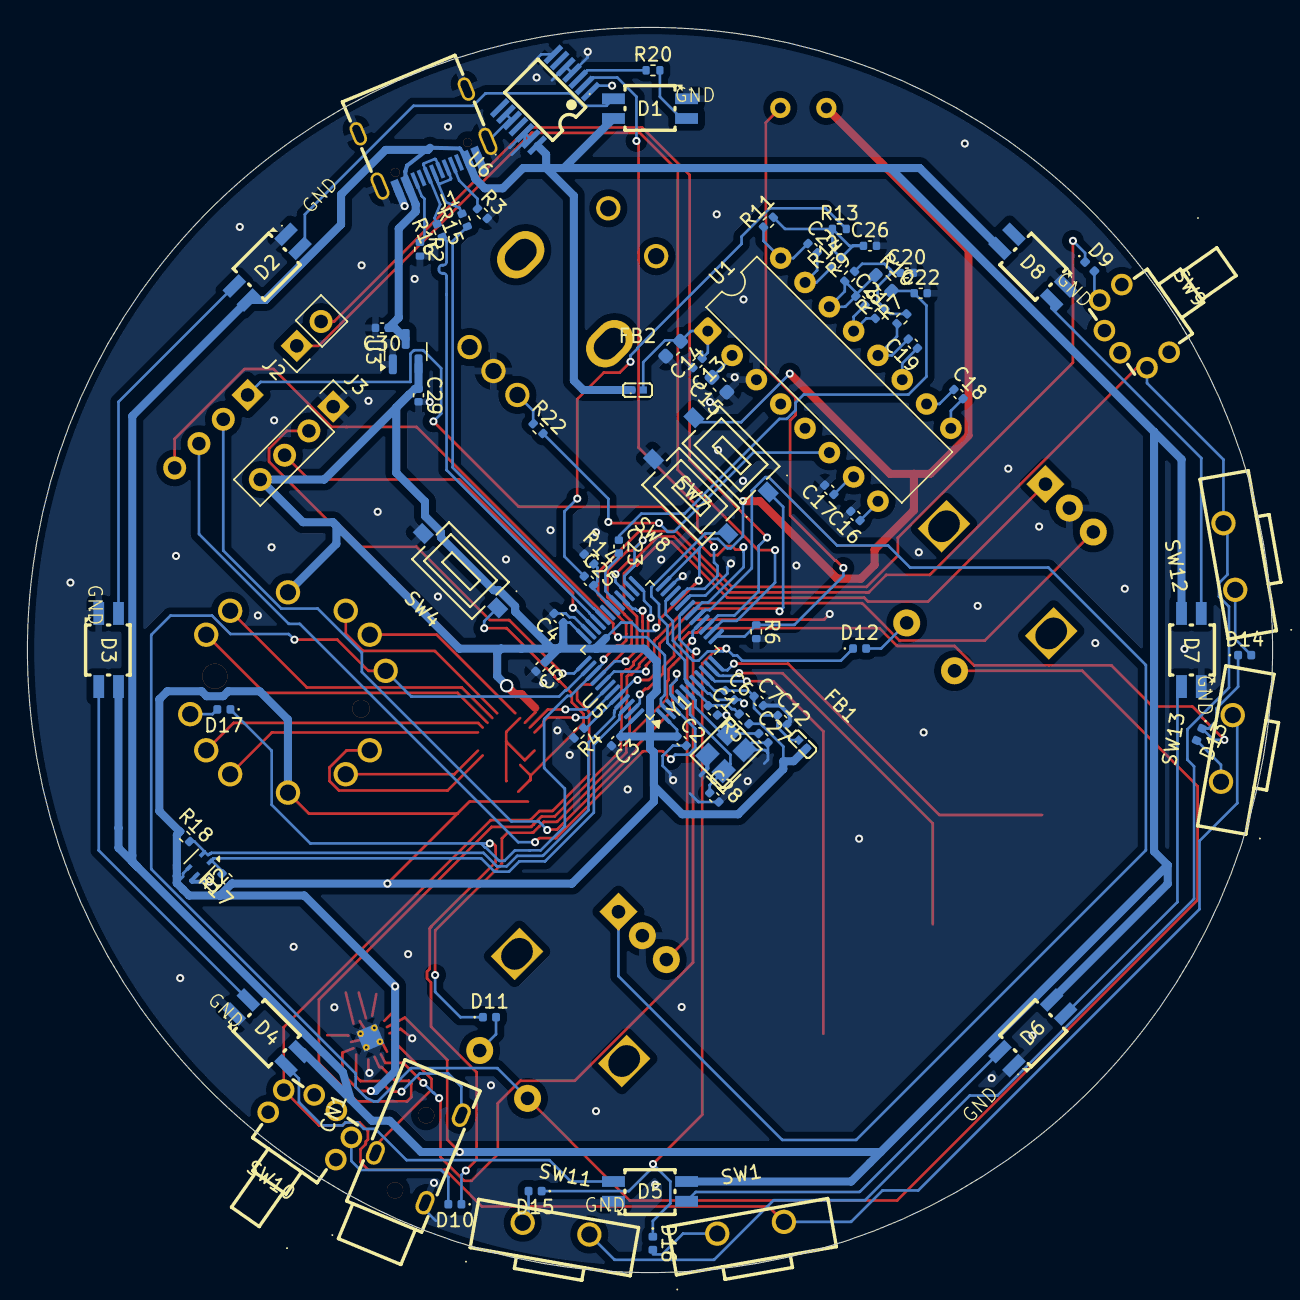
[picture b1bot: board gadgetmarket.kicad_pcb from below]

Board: 2 copper layers, 92.0 x 92.0 mm, 98 parts (83 on the bottom side), 93 nets.

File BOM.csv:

Id,Designator,Footprint,Quantity,Designation,Supplier and ref
1,U4,QFN-20-1EP_4x4mm_P0.5mm_EP2.7x2.7mm,1,MCP23008-xML,https://www.lcsc.com/product-detail/C144211.html?spm=wm.gwc.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
2,C10,C_0402_1005Metric,1,2.2uF,https://www.lcsc.com/product-detail/C170151.html?s_z=n_q_t_c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
3,SW3,RotaryEncoder_Alps_EC12E-Switch_Vertical_H20mm,1,volume,https://www.lcsc.com/product-detail/C255515.html?s_z=n_q_t_e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
4,J4,PinHeader_1x04_P2.54mm_Vertical,1,weaker pins,no part
5,"C31,C32,C17,C3,C2,C4,C13,C18,C1,C19,C16,C6",C_0402_1005Metric,12,100nF,https://www.lcsc.com/product-detail/C60474.html?s_z=n_q_t_ca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
6,"R19,R5,R11,R8,R6",R_0402_1005Metric,5,10K,https://www.lcsc.com/product-detail/C60490.html?s_z=n_q_t_re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
7,"C8,C9,C7",C_0402_1005Metric,3,1uF,https://www.lcsc.com/product-detail/C87145.html?s_z=n_q_t_ca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
8,"REF**,REF**,REF**",capacitive touch button 10mm,3,capacitive touch button 10mm,no part
9,R21,SW-TH_PRS11R-415F-S103B1,1,20K,https://www.lcsc.com/product-detail/C17371045.html?spm=wm.gw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
10,R1,R_LDR_5.1x4.3mm_P3.4mm_Vertical,1,R_Photo,https://www.lcsc.com/product-detail/C125630.html?spm=wm.gwc.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
11,U7,WQFN-16-1EP_3x3mm_P0.5mm_EP1.6x1.6mm_ThermalVias,1,TPA6132A2RTE,https://www.lcsc.com/product-detail/C69901.html?s_z=n_q_TPA6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
12,SW2,RotaryEncoder_Alps_EC12E-Switch_Vertical_H20mm,1,pitch,https://www.lcsc.com/product-detail/C255515.html?s_z=n_q_t_e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
13,SW14,SW-TH_RKJXL100401V,1,SW_Rotary_1x8_MP,https://www.lcsc.com/product-detail/C160838.html?spm=wm.gwc.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
14,"C11,C12,C5",C_0402_1005Metric,3,4.7uF,https://www.lcsc.com/product-detail/C368809.html?s_z=n_q_t_c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
15,C25,C_0402_1005Metric,1,4.7uF,https://www.lcsc.com/product-detail/C368809.html?s_z=n_q_t_c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
16,SW7,SW-SMD_L6.1-W3.7-LS8.0-1,1,BOOT,https://www.lcsc.com/product-detail/C49234126.html?spm=wm.gw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
17,"R13,R12,R9,R7",R_0402_1005Metric,4,15K,https://www.lcsc.com/product-detail/C2909322.html?s_z=n_q_t_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
18,"D8,D3,D1,D5,D4,D7,D6,D2",LED-SMD_4P-L3.2-W2.8-LS5.9_SK6812MINI-E,8,SK6812,https://www.lcsc.com/product-detail/C5149201.html?s_z=n_q_l_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
19,U6,TSSOP-14_L5.0-W4.4-P0.65-LS6.4-BL,1,"74HCT125PW,118",https://www.lcsc.com/product-detail/C131316.html?spm=wm.gwc.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
20,J1,USB-C-SMD_G-SWITCH_GT-USB-7010ASV,1,USB_C_Receptacle_USB2.0_14P,https://www.lcsc.com/product-detail/C2988369.html?spm=wm.gwc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
21,SW1,KEY-TH_L12.0-W3.3-P5.00,1,reset,https://www.lcsc.com/product-detail/C2888728.html?spm=wm.gwc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
22,R20,R_0402_1005Metric,1,330,https://www.lcsc.com/product-detail/C105875.html?s_z=n_q_t_r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
23,"D10,D16,D9,D11,D14,D12,D13,D17,D15",D_0402_1005Metric,9,D,https://www.lcsc.com/product-detail/C28646371.html?s_z=n_q_t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
24,R22,R_0402_1005Metric,1,1K,https://www.lcsc.com/product-detail/C106235.html?s_z=n_q_t_r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
25,SW9,SW-TH_XKB5858-Z-E,1,loop 2,https://www.lcsc.com/product-detail/C780038.html?spm=wm.gwc.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
26,CN1,AUDIO-TH_HOOYA_PJ-320,1,trs headphone jack,https://www.lcsc.com/product-detail/C2939180.html?s_z=n_q_C2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
27,U5,LQFP-48_7x7mm_P0.5mm,1,CH32V203C8T6,https://www.lcsc.com/product-detail/C3001172.html?spm=wm.gwc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
28,"C30,C29",C_0402_1005Metric,2,10uF,https://www.lcsc.com/product-detail/C315248.html?s_z=n_q_t_c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
29,C23,C_0402_1005Metric,1,10uF,https://www.lcsc.com/product-detail/C315248.html?s_z=n_q_t_c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
30,U2,Sensirion_DFN-4_1.5x1.5mm_P0.8mm_SHT4x_NoCentralPad,1,SHT4x,https://www.lcsc.com/product-detail/C55108905.html?s_z=n_q_t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
31,"C24,C21",C_0402_1005Metric,2,560pF,https://www.lcsc.com/product-detail/C315248.html?s_z=n_q_t_c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
32,"C14,C15",C_0402_1005Metric,2,47uf,https://www.lcsc.com/product-detail/C140782.html?s_z=n_q_t_4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
33,"R16,R15",R_0402_1005Metric,2,27,https://www.lcsc.com/product-detail/C2100055.html?s_z=n_q_t_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
34,U3,SOT-23,1,MCP1700x-330xxTT,https://www.lcsc.com/product-detail/C144211.html?spm=wm.gwc.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
35,SW10,SW-TH_XKB5858-Z-E,1,record,https://www.lcsc.com/product-detail/C780038.html?spm=wm.gwc.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
36,"R4,R18,R17",R_0402_1005Metric,3,4.7K,https://www.lcsc.com/product-detail/C105871.html?s_z=n_q_t_r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
37,SW12,KEY-TH_L12.0-W3.3-P5.00,1,free1,https://www.lcsc.com/product-detail/C2888728.html?spm=wm.gwc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
38,SW11,KEY-TH_L12.0-W3.3-P5.00,1,delay,https://www.lcsc.com/product-detail/C2888728.html?spm=wm.gwc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
39,"R3,R2",R_0402_1005Metric,2,5.1K,https://www.lcsc.com/product-detail/C105872.html?s_z=n_q_t_r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
40,SW13,KEY-TH_L12.0-W3.3-P5.00,1,free2,https://www.lcsc.com/product-detail/C2888728.html?spm=wm.gwc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
41,R14,R_0402_1005Metric,1,100K,https://www.lcsc.com/product-detail/C60491.html?s_z=n_q_t_re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
42,"FB2,FB1",L0402,2,FerriteBead_Small,https://www.lcsc.com/product-detail/C17701320.html?spm=wm.gw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
43,C22,C_0402_1005Metric,1,10nF,https://www.lcsc.com/product-detail/C15195.html?s_z=n_q_t_ca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
44,U1,DIP-16_W7.62mm,1,PT2399,https://www.lcsc.com/product-detail/C84963.html?s_z=n_q_x_pt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
45,"C20,C26",C_0402_1005Metric,2,5.6nF,https://www.lcsc.com/product-detail/C281760.html?s_z=n_q_t_c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
46,J2,PinHeader_1x02_P2.54mm_Vertical,1,analog,no part
47,SW8,SW-SMD_L6.1-W3.7-LS8.0-1,1,RESET,https://www.lcsc.com/product-detail/C49234126.html?spm=wm.gw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
48,"C28,C27",C_0402_1005Metric,2,12pF,https://www.lcsc.com/product-detail/C26406.html?s_z=n_q_t_ca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
49,Y1,CRYSTAL-SMD_4P-L3.2-W2.5-BL,1,8MHz,https://www.lcsc.com/product-detail/C2682775.html?spm=wm.gwc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
50,SW4,SW-SMD_L6.1-W3.7-LS8.0-1,1,reset2,https://www.lcsc.com/product-detail/C49234126.html?spm=wm.gw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
51,R10,R_0603_1608Metric,1,2.7K,https://www.lcsc.com/product-detail/C2907008.html?s_z=n_q_t_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
52,J3,PinHeader_1x04_P2.54mm_Vertical,1,debug header,no part
